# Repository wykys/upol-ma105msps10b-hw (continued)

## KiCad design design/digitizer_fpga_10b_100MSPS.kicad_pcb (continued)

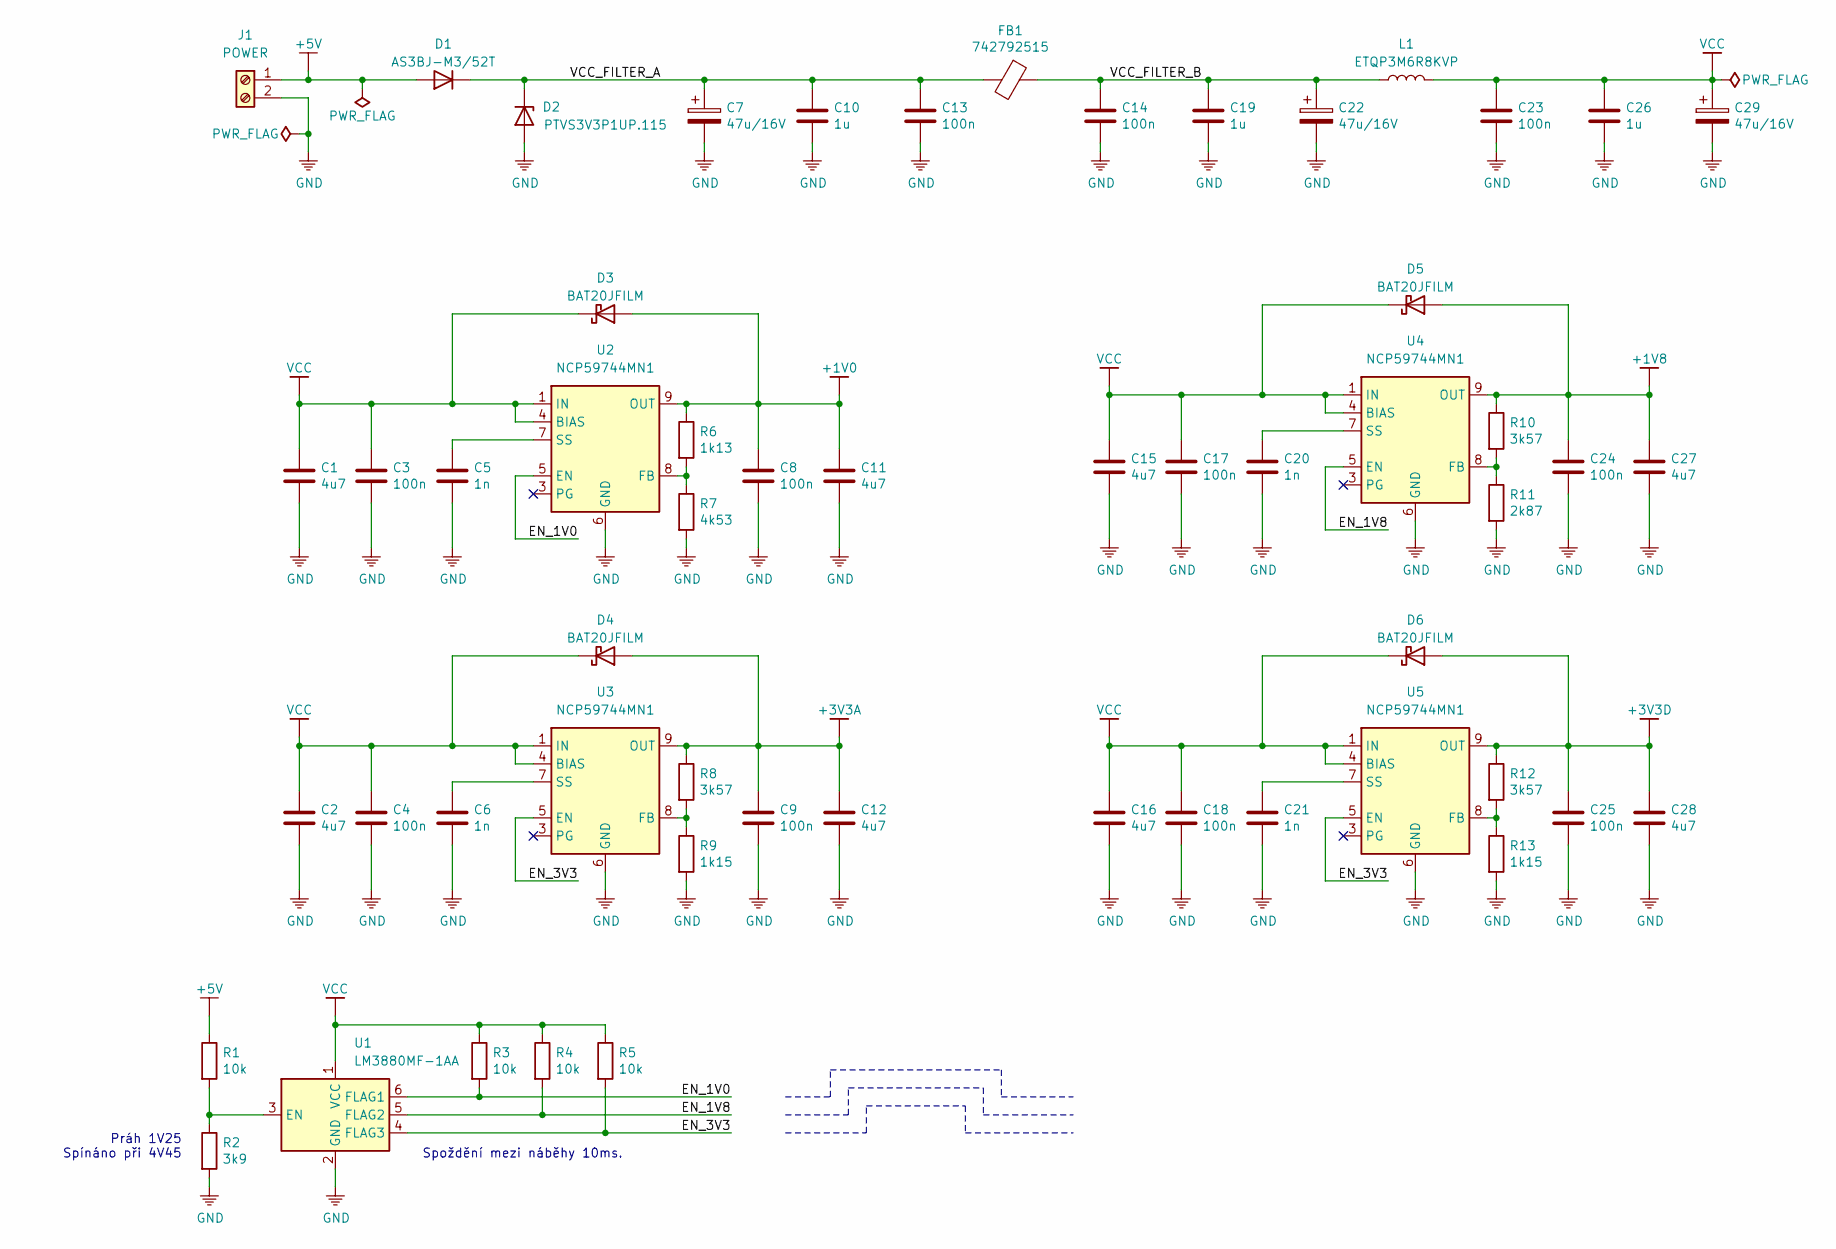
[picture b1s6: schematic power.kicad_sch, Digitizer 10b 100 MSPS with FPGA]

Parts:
C1, C2, C11, C12, C15, C16, C27, C28: 4u7; C_0402_1005Metric
C3, C4, C8, C9, C13, C14, C17, C18, C23, C24, C25: 100n; C_0402_1005Metric
C5, C6, C20, C21: 1n; C_0402_1005Metric
C7, C22, C29: 47u/16V; CP_EIA-7343-31_Kemet-D
C10, C19, C26: 1u; C_0402_1005Metric
D1: AS3BJ-M3/52T; D_SMB
D2: PTVS3V3P1UP.115; D_SOD-128
D3, D4, D5, D6: BAT20JFILM; D_SOD-323
FB1: 742792515; L_1812_4532Metric
J1: POWER; PhoenixContact_MC_1,5_2-G-3.5_1x02_P3.50mm_Horizontal
L1: ETQP3M6R8KVP; L_Bourns_SRN6045TA
R1, R3, R4, R5: 10k; R_0603_1608Metric
R2: 3k9; R_0603_1608Metric
R6: 1k13; R_0603_1608Metric
R7: 4k53; R_0603_1608Metric
R8, R10, R12: 3k57; R_0603_1608Metric
R9, R13: 1k15; R_0603_1608Metric
R11: 2k87; R_0603_1608Metric
U1: LM3880MF-1AA; SOT-23-6
U2, U3, U4, U5: NCP59744MN1; DFN-10-1EP_3x3mm_P0.5mm_EP1.7x2.5mm

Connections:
+1V0: C8.1, C11.1, D3.2 (A), R6.1, U2.9 (OUT), U2.10 (OUT); also elsewhere on the board
+1V8: C24.1, C27.1, D5.2 (A), R10.1, U4.9 (OUT), U4.10 (OUT); also elsewhere on the board
+3V3A: C9.1, C12.1, D4.2 (A), R8.1, U3.9 (OUT), U3.10 (OUT); also elsewhere on the board
+3V3D: C25.1, C28.1, D6.2 (A), R12.1, U5.9 (OUT), U5.10 (OUT); also elsewhere on the board
+5V: D1.2 (A), J1.1, R1.1
/Power/EN_1V0: R3.2, U1.6 (FLAG1), U2.5 (EN)
/Power/EN_1V8: R4.2, U1.5 (FLAG2), U4.5 (EN)
/Power/EN_3V3: R5.2, U1.4 (FLAG3), U3.5 (EN), U5.5 (EN)
/Power/VCC_FILTER_A: C7.1, C10.1, C13.1, D1.1 (K), D2.1 (K), FB1.2
/Power/VCC_FILTER_B: C14.1, C19.1, C22.1, FB1.1, L1.1
GND: C1.2, C2.2, C3.2, C4.2, C5.2, C6.2, C7.2, C8.2, C9.2, C10.2, C11.2, C12.2, C13.2, C14.2, C15.2, C16.2, C17.2, C18.2, C19.2, C20.2, C21.2, C22.2, C23.2, C24.2, C25.2, C26.2, C27.2, C28.2, C29.2, D2.2 (A), J1.2, R2.2, R7.2, R9.2, R11.2, R13.2, U1.2 (GND), U2.6 (GND), U2.11 (EP), U3.6 (GND), U3.11 (EP), U4.6 (GND), U4.11 (EP), U5.6 (GND), U5.11 (EP); also elsewhere on the board
IN: C1.1, C2.1, C3.1, C4.1, C15.1, C16.1, C17.1, C18.1, C23.1, C26.1, C29.1, D3.1 (K), D4.1 (K), D5.1 (K), D6.1 (K), L1.2, R3.1, R4.1, R5.1, U1.1 (VCC), U2.1 (IN), U2.2 (IN), U2.4 (BIAS), U3.1 (IN), U3.2 (IN), U3.4 (BIAS), U4.1 (IN), U4.2 (IN), U4.4 (BIAS), U5.1 (IN), U5.2 (IN), U5.4 (BIAS)
unnamed: C5.1, U2.7 (SS)
unnamed: C6.1, U3.7 (SS)
unnamed: C20.1, U4.7 (SS)
unnamed: C21.1, U5.7 (SS)
unnamed: R1.2, R2.1, U1.3 (EN)
unnamed: R6.2, R7.1, U2.8 (FB)
unnamed: R8.2, R9.1, U3.8 (FB)
unnamed: R10.2, R11.1, U4.8 (FB)
unnamed: R12.2, R13.1, U5.8 (FB)

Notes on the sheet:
Práh 1V25 Spínáno při 4V45
Spoždění mezi náběhy 10ms.

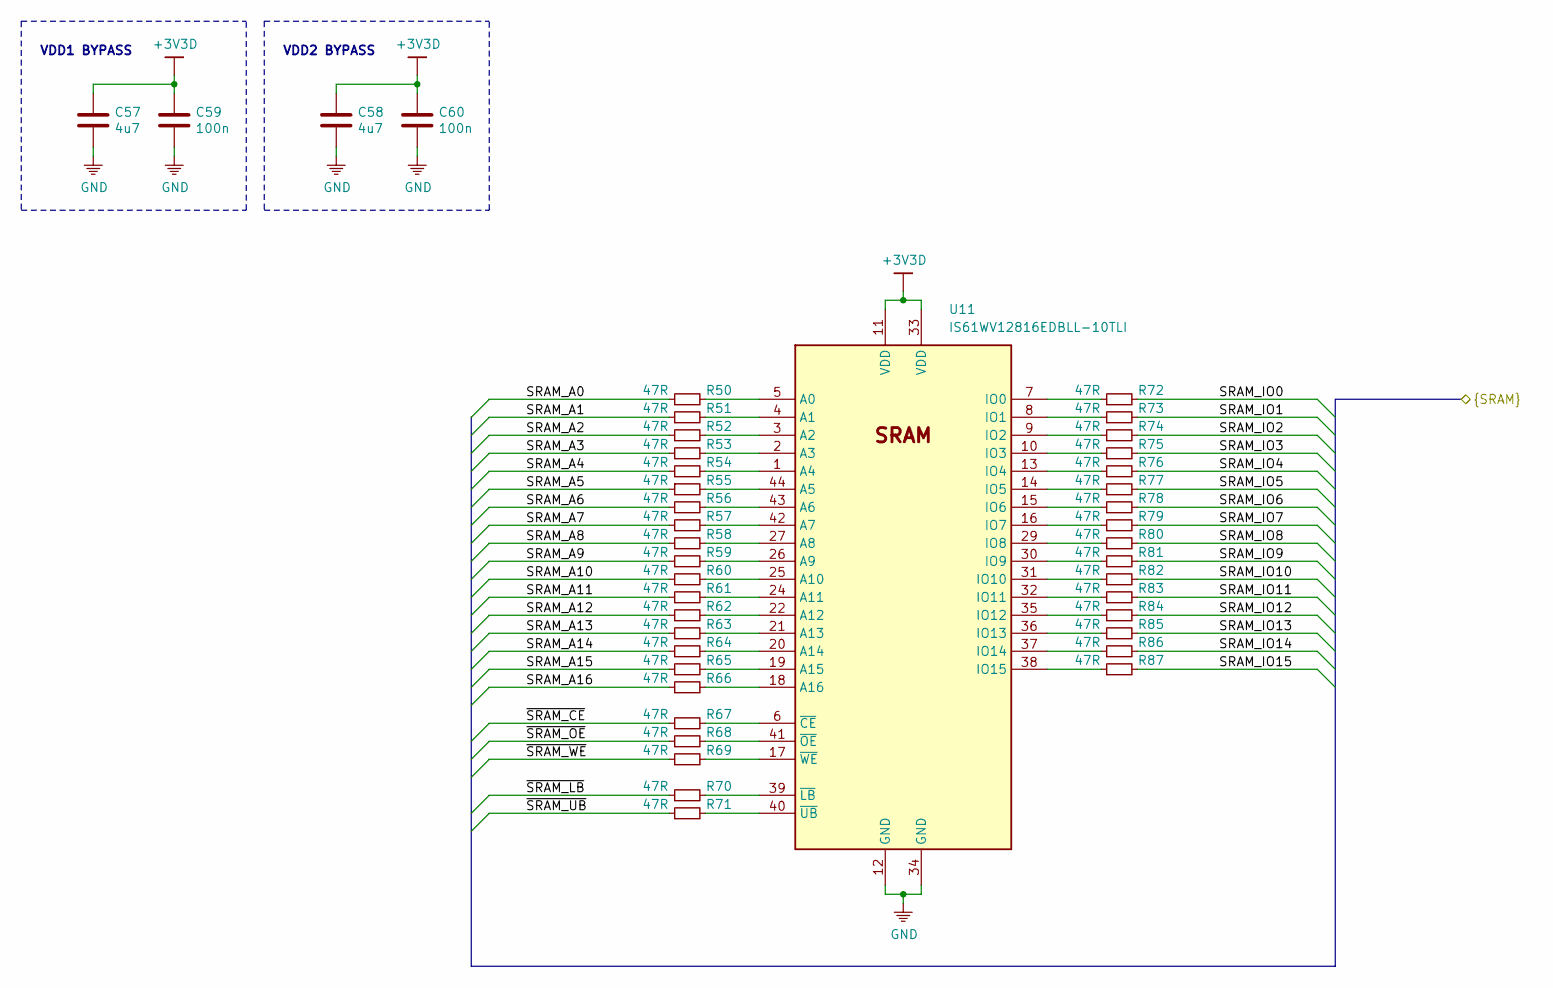
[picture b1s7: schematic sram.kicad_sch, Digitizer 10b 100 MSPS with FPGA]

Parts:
C57, C58: 4u7; C_0402_1005Metric
C59, C60: 100n; C_0402_1005Metric
R50, R51, R52, R53, R54, R55, R56, R57, R58, R59, R60, R61, R62, R63, R64, R65, R66, R67, R68, R69, R70, R71, R72, R73, R74, R75, R76, R77, R78, R79, R80, R81, R82, R83, R84, R85, R86, R87: 47R; R_0402_1005Metric
U11: IS61WV12816EDBLL-10TLI; TSOP-II-44_10.16x18.41mm_P0.8mm

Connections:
+3V3D: C57.1, C58.1, C59.1, C60.1, U11.11 (VDD), U11.33 (VDD); also elsewhere on the board
/FPGA/SRAM_A0: R50.1; also elsewhere on the board
/FPGA/SRAM_A1: R51.1; also elsewhere on the board
/FPGA/SRAM_A2: R52.1; also elsewhere on the board
/FPGA/SRAM_A3: R53.1; also elsewhere on the board
/FPGA/SRAM_A4: R54.1; also elsewhere on the board
/FPGA/SRAM_A5: R55.1; also elsewhere on the board
/FPGA/SRAM_A6: R56.1; also elsewhere on the board
/FPGA/SRAM_A7: R57.1; also elsewhere on the board
/FPGA/SRAM_A8: R58.1; also elsewhere on the board
/FPGA/SRAM_A9: R59.1; also elsewhere on the board
/FPGA/SRAM_A10: R60.1; also elsewhere on the board
/FPGA/SRAM_A11: R61.1; also elsewhere on the board
/FPGA/SRAM_A12: R62.1; also elsewhere on the board
/FPGA/SRAM_A13: R63.1; also elsewhere on the board
/FPGA/SRAM_A14: R64.1; also elsewhere on the board
/FPGA/SRAM_A15: R65.1; also elsewhere on the board
/FPGA/SRAM_A16: R66.1; also elsewhere on the board
/FPGA/SRAM_IO0: R72.2; also elsewhere on the board
/FPGA/SRAM_IO1: R73.2; also elsewhere on the board
/FPGA/SRAM_IO2: R74.2; also elsewhere on the board
/FPGA/SRAM_IO3: R75.2; also elsewhere on the board
/FPGA/SRAM_IO4: R76.2; also elsewhere on the board
/FPGA/SRAM_IO5: R77.2; also elsewhere on the board
/FPGA/SRAM_IO6: R78.2; also elsewhere on the board
/FPGA/SRAM_IO7: R79.2; also elsewhere on the board
/FPGA/SRAM_IO8: R80.2; also elsewhere on the board
/FPGA/SRAM_IO9: R81.2; also elsewhere on the board
/FPGA/SRAM_IO10: R82.2; also elsewhere on the board
/FPGA/SRAM_IO11: R83.2; also elsewhere on the board
/FPGA/SRAM_IO12: R84.2; also elsewhere on the board
/FPGA/SRAM_IO13: R85.2; also elsewhere on the board
/FPGA/SRAM_IO14: R86.2; also elsewhere on the board
/FPGA/SRAM_IO15: R87.2; also elsewhere on the board
/FPGA/~SRAM_CE: R67.1; also elsewhere on the board
/FPGA/~SRAM_LB: R70.1; also elsewhere on the board
/FPGA/~SRAM_OE: R68.1; also elsewhere on the board
/FPGA/~SRAM_UB: R71.1; also elsewhere on the board
/FPGA/~SRAM_WE: R69.1; also elsewhere on the board
GND: C57.2, C58.2, C59.2, C60.2, U11.12 (GND), U11.34 (GND); also elsewhere on the board
unnamed: R50.2, U11.5 (A0)
unnamed: R51.2, U11.4 (A1)
unnamed: R52.2, U11.3 (A2)
unnamed: R53.2, U11.2 (A3)
unnamed: R54.2, U11.1 (A4)
unnamed: R55.2, U11.44 (A5)
unnamed: R56.2, U11.43 (A6)
unnamed: R57.2, U11.42 (A7)
unnamed: R58.2, U11.27 (A8)
unnamed: R59.2, U11.26 (A9)
unnamed: R60.2, U11.25 (A10)
unnamed: R61.2, U11.24 (A11)
unnamed: R62.2, U11.22 (A12)
unnamed: R63.2, U11.21 (A13)
unnamed: R64.2, U11.20 (A14)
unnamed: R65.2, U11.19 (A15)
unnamed: R66.2, U11.18 (A16)
unnamed: R67.2, U11.6 (~CE)
unnamed: R68.2, U11.41 (~OE)
unnamed: R69.2, U11.17 (~WE)
unnamed: R70.2, U11.39 (~LB)
unnamed: R71.2, U11.40 (~UB)
unnamed: R72.1, U11.7 (IO0)
unnamed: R73.1, U11.8 (IO1)
unnamed: R74.1, U11.9 (IO2)
unnamed: R75.1, U11.10 (IO3)
unnamed: R76.1, U11.13 (IO4)
unnamed: R77.1, U11.14 (IO5)
unnamed: R78.1, U11.15 (IO6)
unnamed: R79.1, U11.16 (IO7)
unnamed: R80.1, U11.29 (IO8)
unnamed: R81.1, U11.30 (IO9)
unnamed: R82.1, U11.31 (IO10)
unnamed: R83.1, U11.32 (IO11)
unnamed: R84.1, U11.35 (IO12)
unnamed: R85.1, U11.36 (IO13)
unnamed: R86.1, U11.37 (IO14)
unnamed: R87.1, U11.38 (IO15)

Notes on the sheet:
VDD1 BYPASS
VDD2 BYPASS

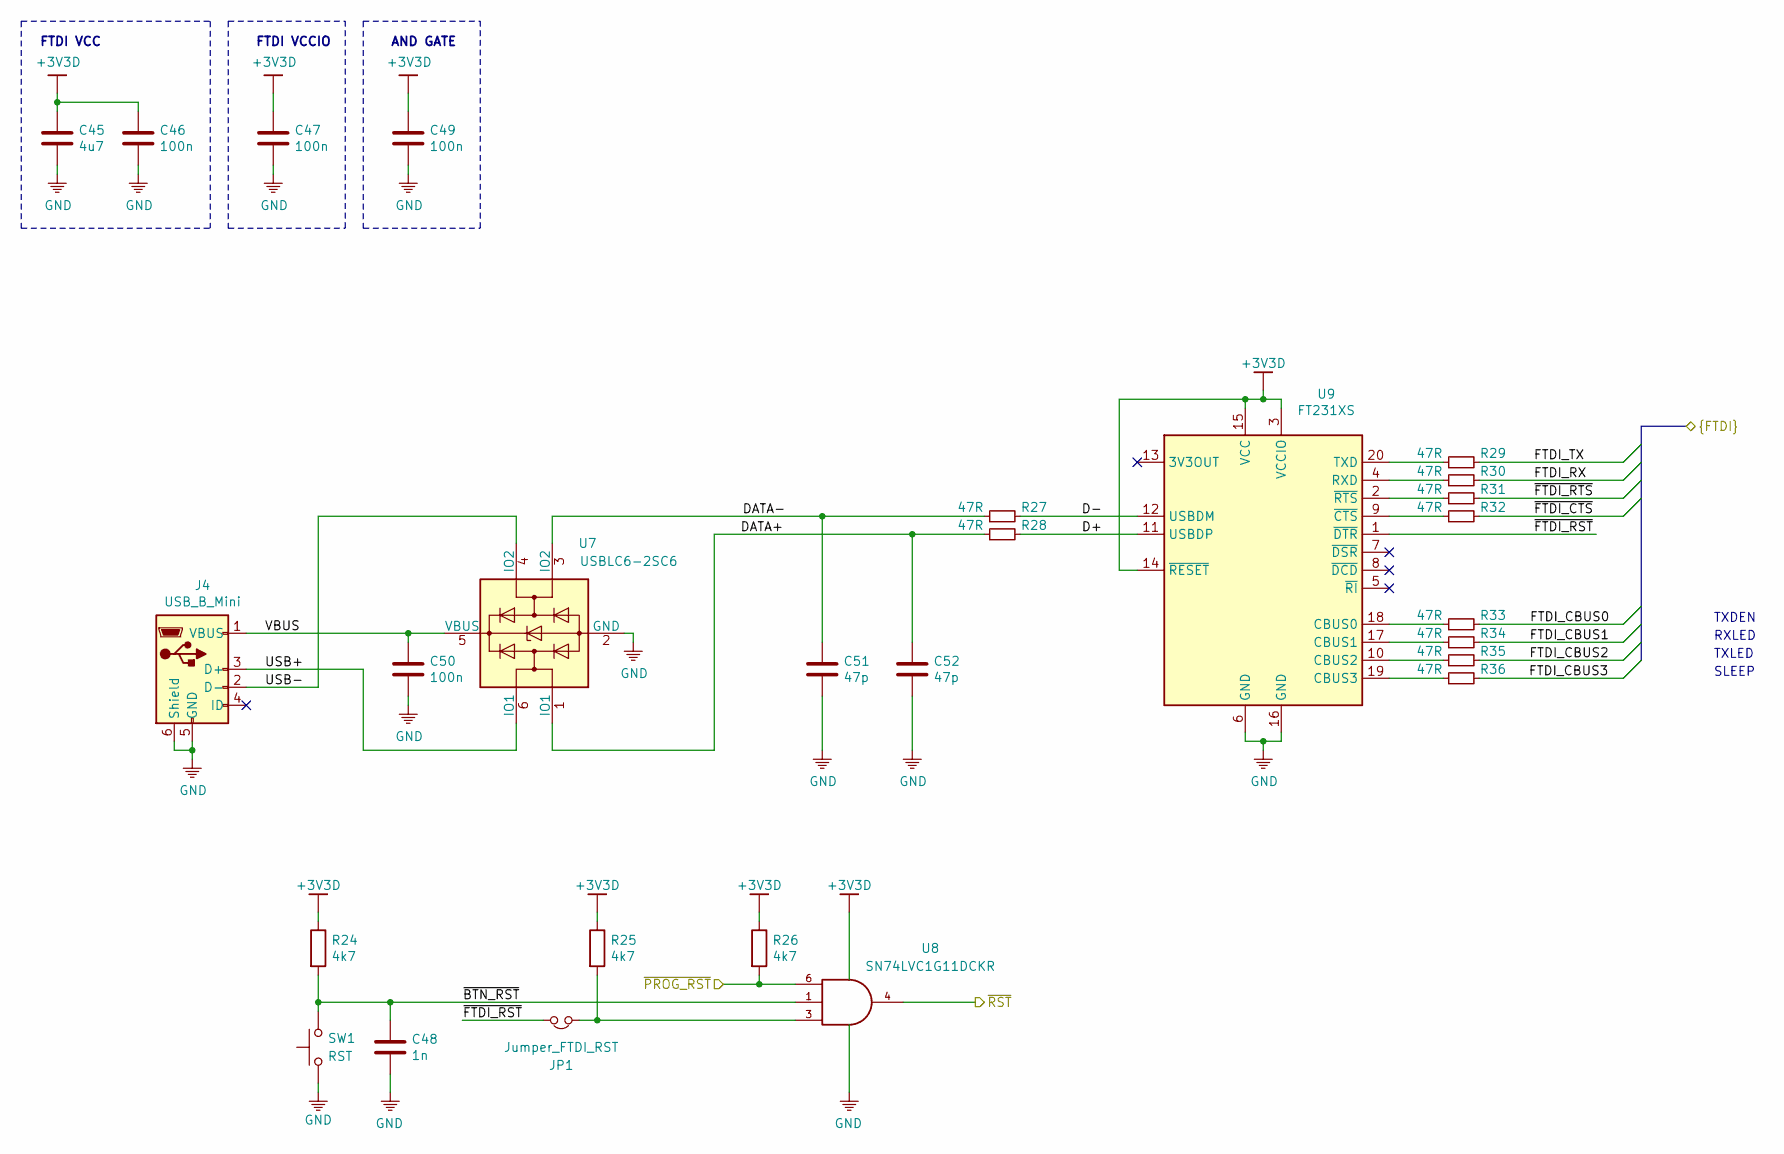
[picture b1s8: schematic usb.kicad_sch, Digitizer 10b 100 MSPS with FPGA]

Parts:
C45: 4u7; C_0402_1005Metric
C46, C47, C49, C50: 100n; C_0402_1005Metric
C48: 1n; C_0402_1005Metric
C51, C52: 47p; C_0402_1005Metric
J4: USB_B_Mini; USB_Mini-B_Lumberg_2486_01_Horizontal
JP1: Jumper_FTDI_RST; PinHeader_1x02_P2.54mm_Vertical
R24, R25, R26: 4k7; R_0603_1608Metric
R27, R28, R29, R30, R31, R32, R33, R34, R35, R36: 47R; R_0402_1005Metric
SW1: RST; SW_SPST_CK_RS282G05A3
U7: USBLC6-2SC6; SOT-23-6
U8: SN74LVC1G11DCKR; SOT-363_SC-70-6
U9: FT231XS; SSOP-20_3.9x8.7mm_P0.635mm

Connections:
+3V3D: C45.1, C46.1, C47.1, C49.1, R24.1, R25.1, R26.1, U8.5 (VCC), U9.3 (VCCIO), U9.14 (~RESET), U9.15 (VCC); also elsewhere on the board
/FPGA/~RST: U8.4; also elsewhere on the board
/MCU/FTDI_CBUS0: R33.2; also elsewhere on the board
/MCU/FTDI_CBUS1: R34.2; also elsewhere on the board
/MCU/FTDI_CBUS2: R35.2; also elsewhere on the board
/MCU/FTDI_CBUS3: R36.2; also elsewhere on the board
/MCU/FTDI_RX: R30.2; also elsewhere on the board
/MCU/FTDI_TX: R29.2; also elsewhere on the board
/MCU/~FTDI_CTS: R32.2; also elsewhere on the board
/MCU/~FTDI_RTS: R31.2; also elsewhere on the board
/MCU/~PROG_RST: R26.2, U8.6; also elsewhere on the board
/USB/D+: R28.2, U9.11 (USBDP)
/USB/D-: R27.2, U9.12 (USBDM)
/USB/DATA+: C52.1, R28.1, U7.1 (IO1)
/USB/DATA-: C51.1, R27.1, U7.3 (IO2)
/USB/USB+: J4.3 (D+), U7.6 (IO1)
/USB/USB-: J4.2 (D-), U7.4 (IO2)
/USB/VBUS: C50.1, J4.1 (VBUS), U7.5 (VBUS)
/USB/~BTN_RST: C48.1, R24.2, SW1.2, U8.1
/USB/~FTDI_RST: JP1.1, U9.1 (~DTR)
GND: C45.2, C46.2, C47.2, C48.2, C49.2, C50.2, C51.2, C52.2, J4.5 (GND), J4.6 (Shield), SW1.1, U7.2 (GND), U8.2 (GND), U9.6 (GND), U9.16 (GND); also elsewhere on the board
unnamed: JP1.2, R25.2, U8.3
unnamed: R29.1, U9.20 (TXD)
unnamed: R30.1, U9.4 (RXD)
unnamed: R31.1, U9.2 (~RTS)
unnamed: R32.1, U9.9 (~CTS)
unnamed: R33.1, U9.18 (CBUS0)
unnamed: R34.1, U9.17 (CBUS1)
unnamed: R35.1, U9.10 (CBUS2)
unnamed: R36.1, U9.19 (CBUS3)

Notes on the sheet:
FTDI VCC
FTDI VCCIO
AND GATE
TXDEN
RXLED
TXLED
SLEEP

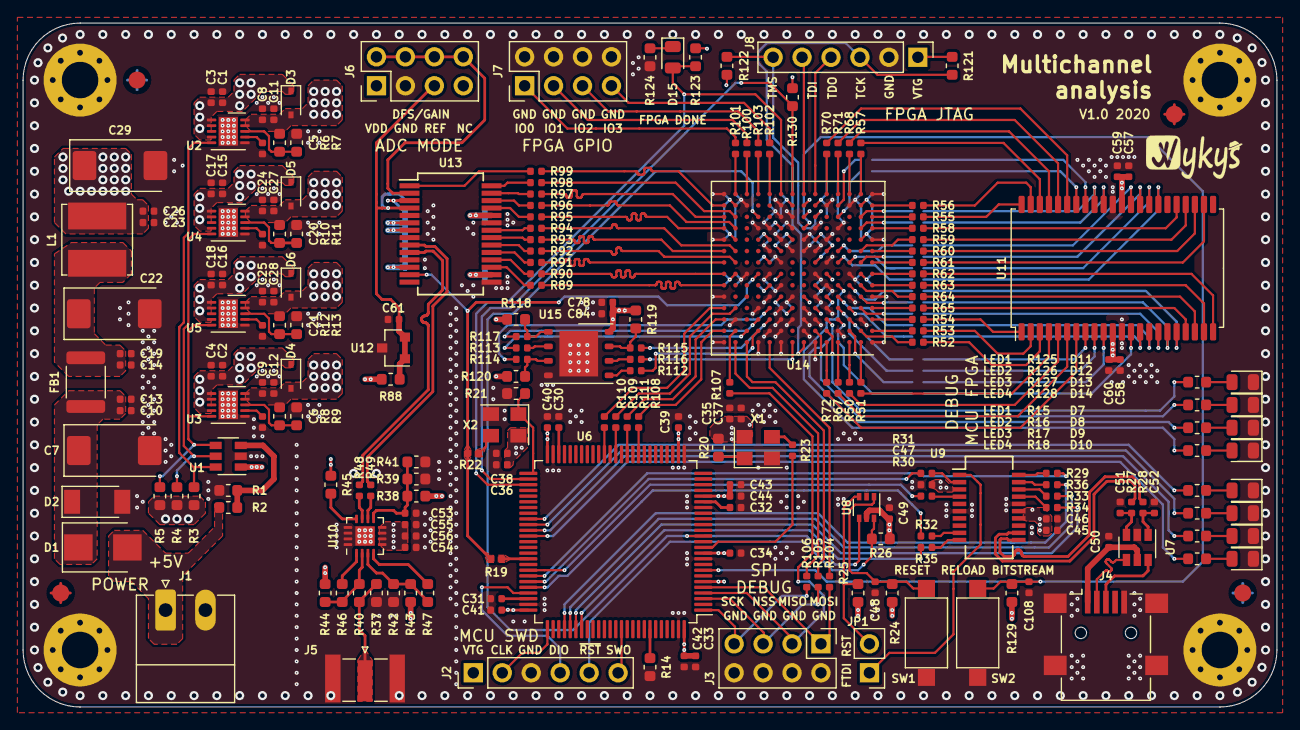
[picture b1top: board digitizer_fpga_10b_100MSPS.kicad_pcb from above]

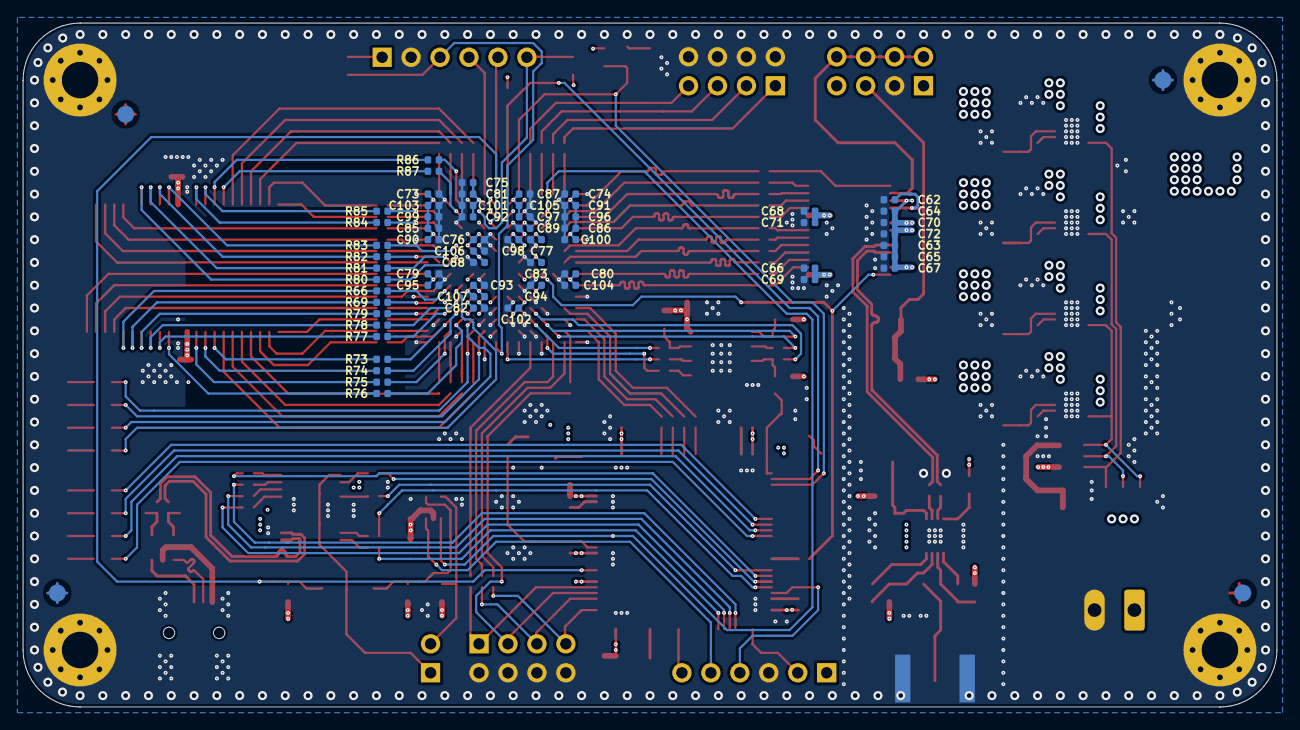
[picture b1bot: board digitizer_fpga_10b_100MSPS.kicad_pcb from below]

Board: 4 copper layers, 110.0 x 60.0 mm, 296 parts (65 on the bottom side), 234 nets.

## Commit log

2020-05-06 Updated .gitignore
2020-05-06 Added design from old repository
2020-05-06 Added LAN placement
2020-05-06 Added ADC placement
2020-05-06 Fixed LNA power
2020-05-06 Added FTDI placemnt
2020-05-06 Added MCU placement
2020-05-06 Added SRAM placement
2020-05-06 Added basic FPGA placement
2020-05-06 Added buses that were removed when converting from the old format
2020-05-07 Added FPGA placement
2020-05-07 Updated placement
2020-05-07 Added some design rules
2020-05-07 Added support lines for BGA fanout
2020-05-08 Created Basic polygons
2020-05-08 Added LDO output polygons
2020-05-08 Moved FPGA capacitors
2020-05-08 Changed FPGA via diamertal to 350um
2020-05-08 Connected FPGA GND
2020-05-08 Added some polygons and connected ADC
2020-05-08 Added power polygons
2020-05-08 Updated LDO VCC input polygons
2020-05-08 Fixed IN vias
2020-05-08 Added power manager layout
2020-05-08 Moved some resistors
2020-05-09 Added ground polygon on TOP layer
2020-05-09 Added part SRAM layout
2020-05-09 Added part SRAM layout
2020-05-10 Chenged to 4 layers
2020-05-10 Chenged 350um track to 200um
2020-05-10 Updated ADC layout
2020-05-10 Added some tracks
2020-05-11 Added datasheet
2020-05-11 Changed TP footprint
2020-05-11 Moved ADC
2020-05-11 Updated FLASH placement
2020-05-12 Chenged Rs positions
2020-05-12 Added test RAM layout
2020-05-12 Added USB datasheet
2020-05-12 Added FTDI layout
2020-05-12 Added MCU power layout
2020-05-12 Added LNA layout
2020-05-12 Updated some layout
2020-05-12 Removed legacy rescue and cashe files
2020-05-13 Updated polygons
2020-05-13 Added some layout
2020-05-13 Rename buses from X..0 to 0..X
2020-05-14 Added RAM layout
2020-05-14 Updated layout
2020-05-14 Created new RAM placement and test layout
2020-05-15 Minimalised RAM layout
2020-05-15 Aligned RAM vias
2020-05-15 Upgraded SRAM layout
2020-05-15 Added FPGA LEDs layout
2020-05-15 Updated FLASH layout
2020-05-15 Added MCU LED layout
2020-05-15 Updated FPGA LED layout
2020-05-15 Added SPI connection
2020-05-15 Added bridge connection
2020-05-15 Added USB layout
2020-05-15 Added clock layout
2020-05-15 Added SWD layout
2020-05-15 Added some power layout
2020-05-15 Connected reset to FPGA
2020-05-15 Connected FPGA controll
2020-05-15 Connected ADC jumper
2020-05-15 Fixed some design rules
2020-05-15 Fixed amp test points
2020-05-15 Updated polygons and removed redundant BGA fan out
2020-05-15 Added vias board round
2020-05-15 Small layout update
2020-05-15 Updated power polygons
2020-05-16 Refactored FPGA schematic
2020-05-17 Added external oscilator for FPGA and ADC to schematic
2020-05-17 Added oscilator layout
2020-05-18 Added FTDI RST support
2020-05-18 Fixed MCU RST
2020-05-18 Updated RST layout
2020-05-19 Added some layout updated
2020-05-19 Removed LNA test points
2020-05-19 Added bypass C to RST gate
2020-05-19 Updated SPI layout
2020-05-19 Reannoted schematic
2020-05-19 Updated F.SilkS
2020-05-19 Added LEDs text to F.SilkS
2020-05-19 Added connectors description to F.SilkS
2020-05-19 Added logo and description to F.Silks
2020-05-19 Aligned text to B.SilkS
2020-05-19 Named button reset net
2020-05-19 Added FPGA DONE description to F.SilkS
2020-05-19 Chenged SWD connector from 4 pins to 6 pins
2020-05-19 Added SWD description to F.SilkS
2020-05-20 Updated reset system
2020-05-20 Updates layout
2020-05-20 Added power description to F.SilkS
2020-05-20 Added keepout aeras
2020-05-20 Added fiducials
2020-05-20 Updated fiducials positions
2020-05-20 Updated schematic
2020-05-20 Updated project
2020-05-20 Added SWD label to F.SilkS
2020-05-20 Updated PCB
2020-05-20 Connected USB shield to GND
2020-05-21 Created Gerbers
2020-05-31 Updated LNA
2020-06-07 Added paste clearence -2%
2020-06-07 Updated gerber paste files
2020-06-19 Propagated schematich values changes to PCB
2020-06-19 Updated documentation
2020-06-19 Created BOM
2020-06-23 Updated notes
2020-06-30 Fixed ADC PWRDN problem
2020-07-04 Converted provject form old .pro to .kicad_pro new format
2020-07-28 Added net classes
2020-08-16 Fixed netclass
2020-08-16 Added support scripts
2020-08-17 Fixed project for new ID access in KiCad V6
2020-08-18 Updated SMA 3D model name
2021-01-17 Added ibom
2021-01-17 Fixed 3D path for KiCad V6
2021-01-17 Fixed SCH file format
2021-03-31 Updated to new KiCad file format
2021-03-31 Updated AND symbol
